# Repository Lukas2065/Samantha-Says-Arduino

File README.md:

# Samantha-Says-Arduino v1.0
This project aims to create a real version of the Samantha Says mini game from the Black Ops 1 & Black Ops 3 Moon Zombie map.
## v1.0 Specifics
The project is currently breadboard based. Using the Arduino Uno, connected to 4 switches, 4 resitors and 4 LEDs. It is able to replicate the mini game from the map, with some constraints. These constraints will be addressed in future iterations.
## v1.0 Future Plans
Future plans include, attatching components to a pcb, 3D printing the Samantha Says computers to replicate the mini game, chaning the LEDs from single colour LEDs to RGB LEDs to fully replicate the game. There might also be the possibilty of switching to an Arduino Nano if possible to decrease the size.

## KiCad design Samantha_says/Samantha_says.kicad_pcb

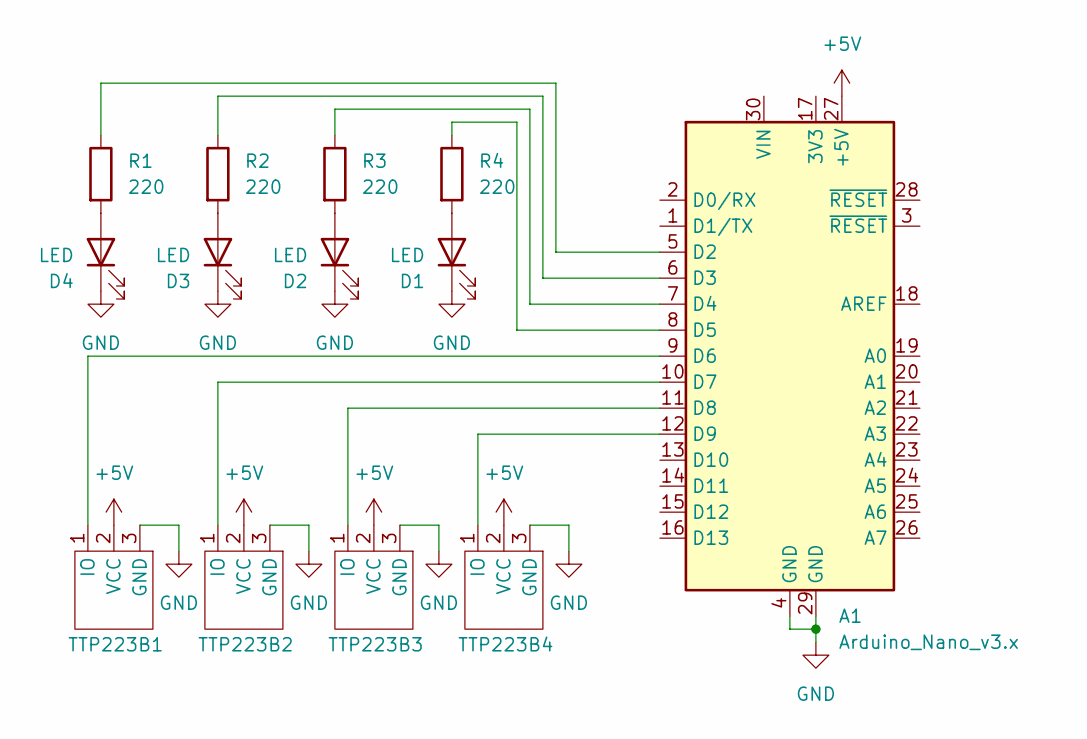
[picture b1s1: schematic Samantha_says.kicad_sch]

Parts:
A1: Arduino_Nano_v3.x; Arduino_Nano
D1, D2, D3, D4: LED; PinHeader_1x02_P2.54mm_Vertical
R1, R2, R3, R4: 220; R_Axial_DIN0207_L6.3mm_D2.5mm_P7.62mm_Horizontal
TTP223B1, TTP223B2, TTP223B3, TTP223B4: TTP223B 2.54mm

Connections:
+5V: A1.27 (+5V), TTP223B1.2 (VCC), TTP223B2.2 (VCC), TTP223B3.2 (VCC), TTP223B4.2 (VCC)
GND: A1.4 (GND), A1.29 (GND), D1.1 (K), D2.1 (K), D3.1 (K), D4.1 (K), TTP223B1.3 (GND), TTP223B2.3 (GND), TTP223B3.3 (GND), TTP223B4.3 (GND)
unnamed: A1.5 (D2), R1.1
unnamed: A1.6 (D3), R2.1
unnamed: A1.7 (D4), R3.1
unnamed: A1.8 (D5), R4.1
unnamed: A1.9 (D6), TTP223B1.1 (IO)
unnamed: A1.10 (D7), TTP223B2.1 (IO)
unnamed: A1.11 (D8), TTP223B3.1 (IO)
unnamed: A1.12 (D9), TTP223B4.1 (IO)
unnamed: D1.2 (A), R4.2
unnamed: D2.2 (A), R3.2
unnamed: D3.2 (A), R2.2
unnamed: D4.2 (A), R1.2

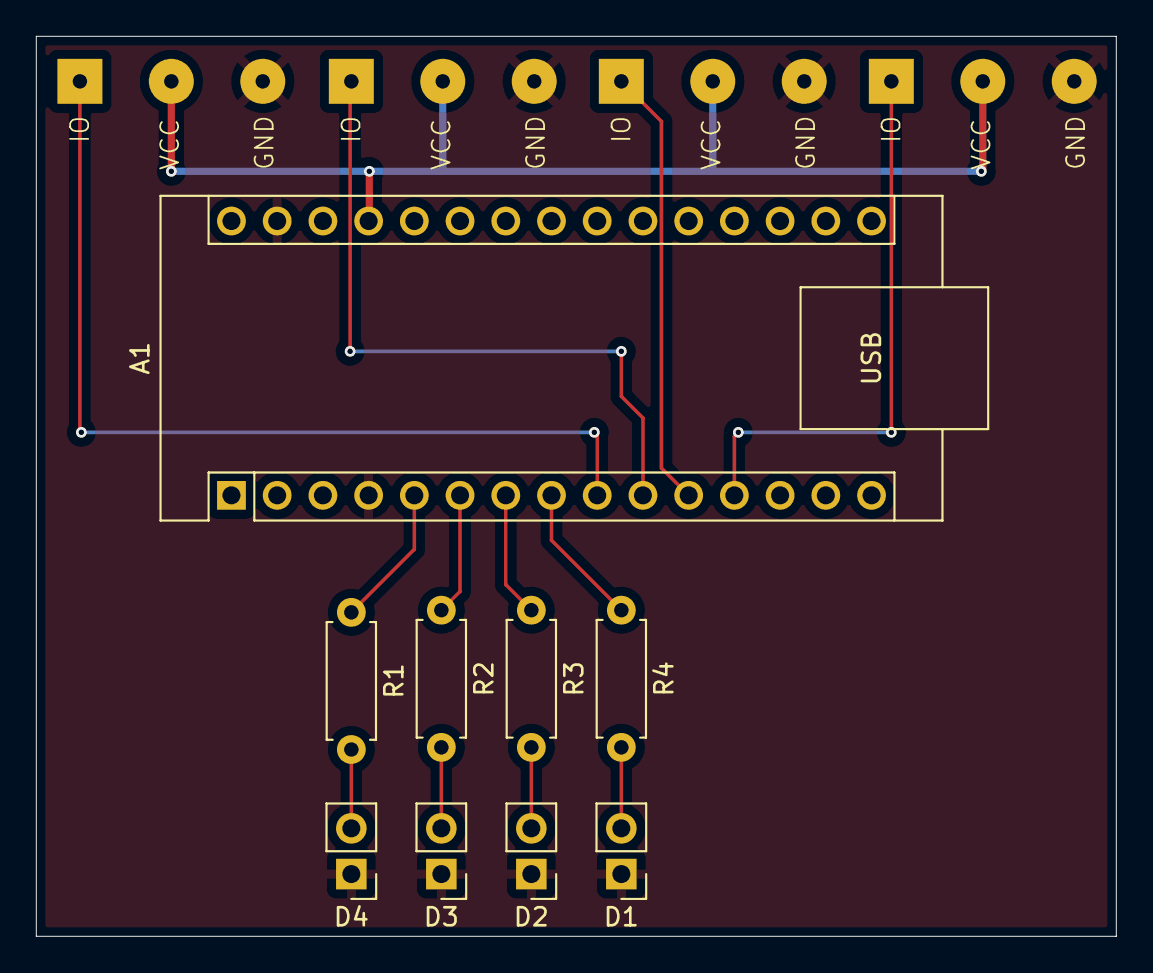
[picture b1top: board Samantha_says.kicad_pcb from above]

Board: 2 copper layers, 60.0 x 50.0 mm, 13 parts (0 on the bottom side), 14 nets.

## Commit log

2026-01-30 Lights up an LEDs with corresponding switches pressed
2026-01-30 Update Samantha-Says.ino
    Created a startup sequence. Created an FSM that does a game start sequence followed by picking a random LED and then allowing the player to press an LED.
2026-01-30 Update Samantha-Says.ino
    The program can now adds a random LED to the sequence after each button press and displays them.
2026-01-31 Update Samantha-Says.ino
    Fixed functionality where user can no longer hold a switch and keep LED light on. If user holds the switch it turns LED on for 1 second and then carries out with rest of operations, if the user is st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
2026-02-01 Update Samantha-Says.ino
    Finished the game. Implemented the checking of user input with the samantha sequence. Also added a success sequence to show player they have got level correct.
2026-02-01 Update README with project overview and specifics
    Added project details and future plans for version 1.0.
2026-02-01 Update Samantha-Says.ino
    Small issue where if the game carried on for long then if there was an incorrect player response then it would still show success sequence and carry on.
2026-02-01 Update Samantha-Says.ino
    Added comments and removed redundant code
2026-02-09 Added schematic for v1.0
    Here is the v1.0 schematic using the Arduino Uno.
2026-04-10 Added schematics for v2.0
2026-04-10 Made PCB for v2.0
2026-04-10 Finished and saved v2.0 pcb
